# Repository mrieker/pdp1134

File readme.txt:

FPGA/ARM board that plugs into Unibus on PDP-11/34.

Provides functionality of the KY-11 console, 124KW memory,
RL-11 disks (RL01/RL02), DL-11 serial port, KW-11 line clock,
RH-11 disks (RP04/RP06), TM-11 tape drive, DELUA ethernet,
PC-11 paper tape reader/punch, DZ-11 serial line mux.

Also contains a PDP-11/34 processor simulator so can test
software without having real processor.

Has a GUI interface (ccode/z11gui) as well as a TCL command line
interface (ccode/z11ctrl) for scripting.

See howto.txt for more information.

Pics of board and gui screen are in boardpic.jpg and guittypic.png,
runningpic.jpg is pic of 10.5" screen mounted on front of PDP-11/34
with Zynq in place of console board.

It uses a ZTurn Zynq 7020 board for the FPGA/ARM processor,
memory, SDCARD, ethernet.  The ARM processor runs the
Raspberry PI OS, with a kernel specific to the Zynq.

The board might work on other PDP-11s, I haven't tested it
with anything else.  The only thing that makes it '34 specific
are the two halt signals.  Other than that, it is just another
Unibus compatible device, fitting in a quad-sized SPC slot.

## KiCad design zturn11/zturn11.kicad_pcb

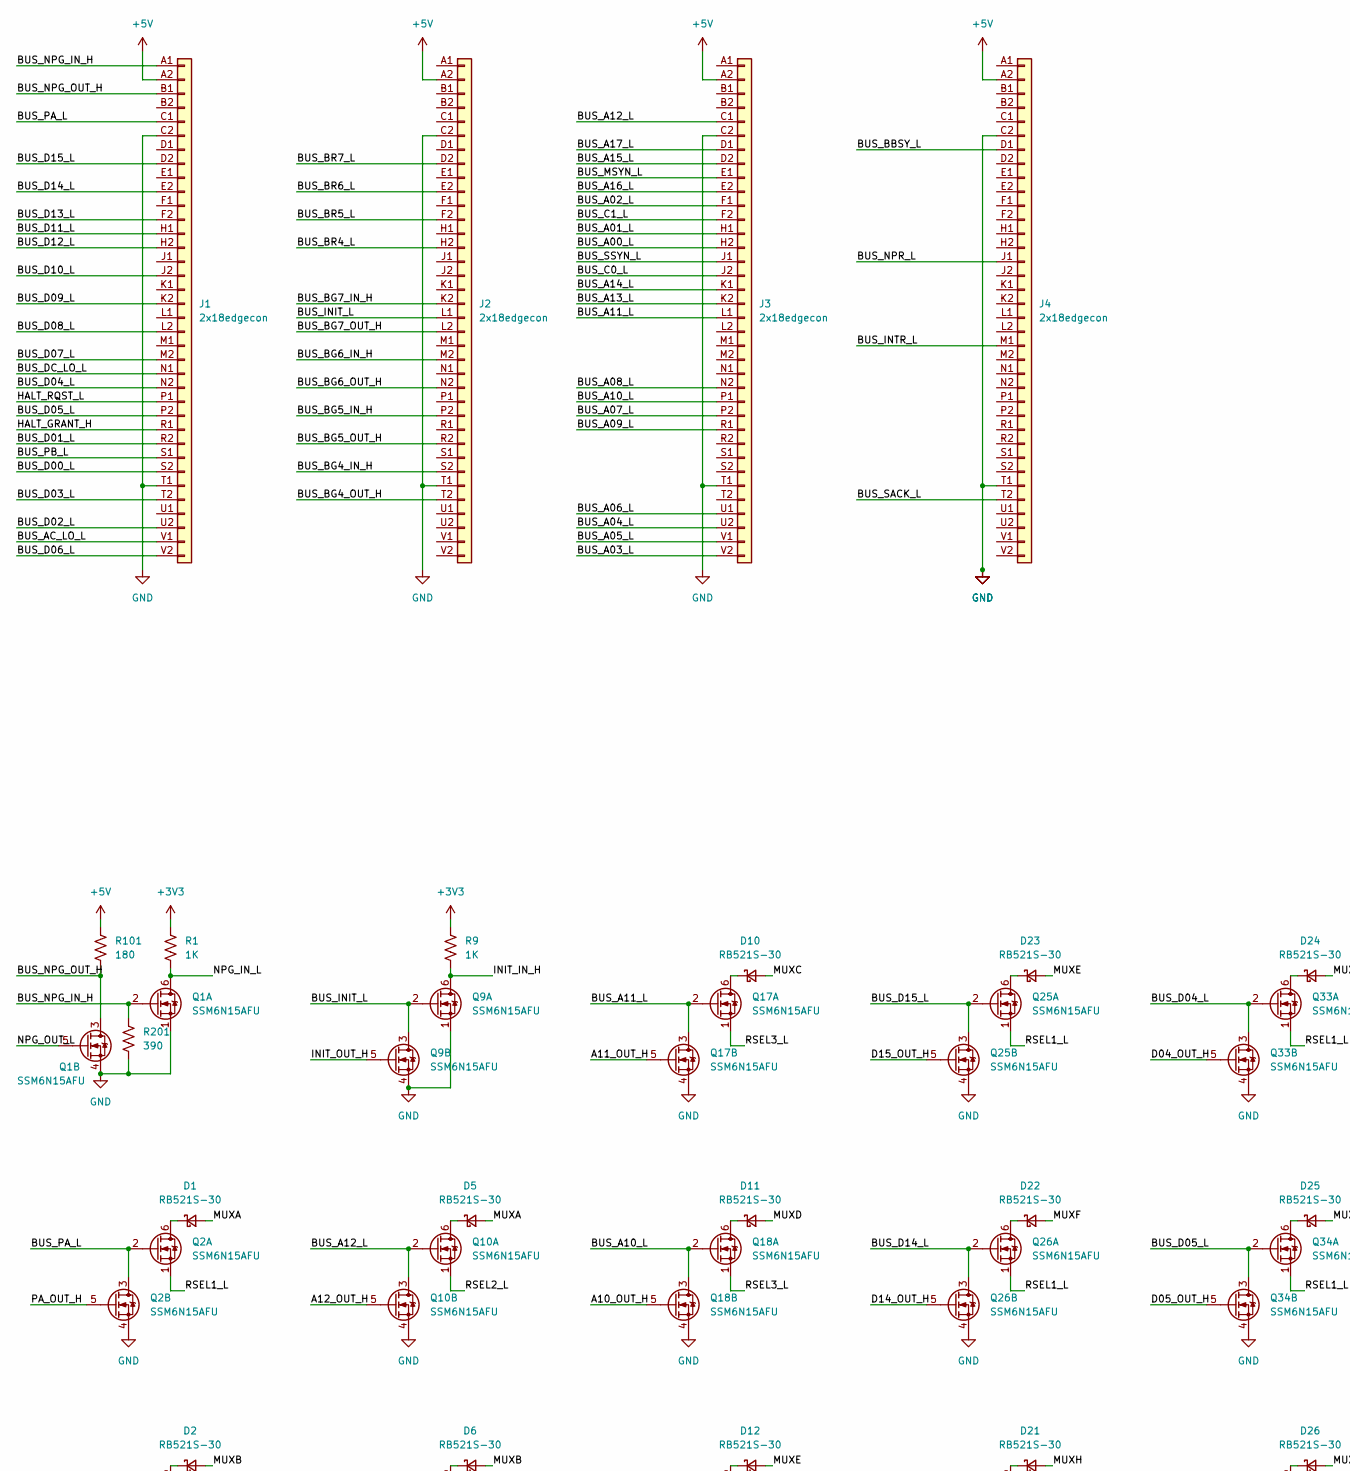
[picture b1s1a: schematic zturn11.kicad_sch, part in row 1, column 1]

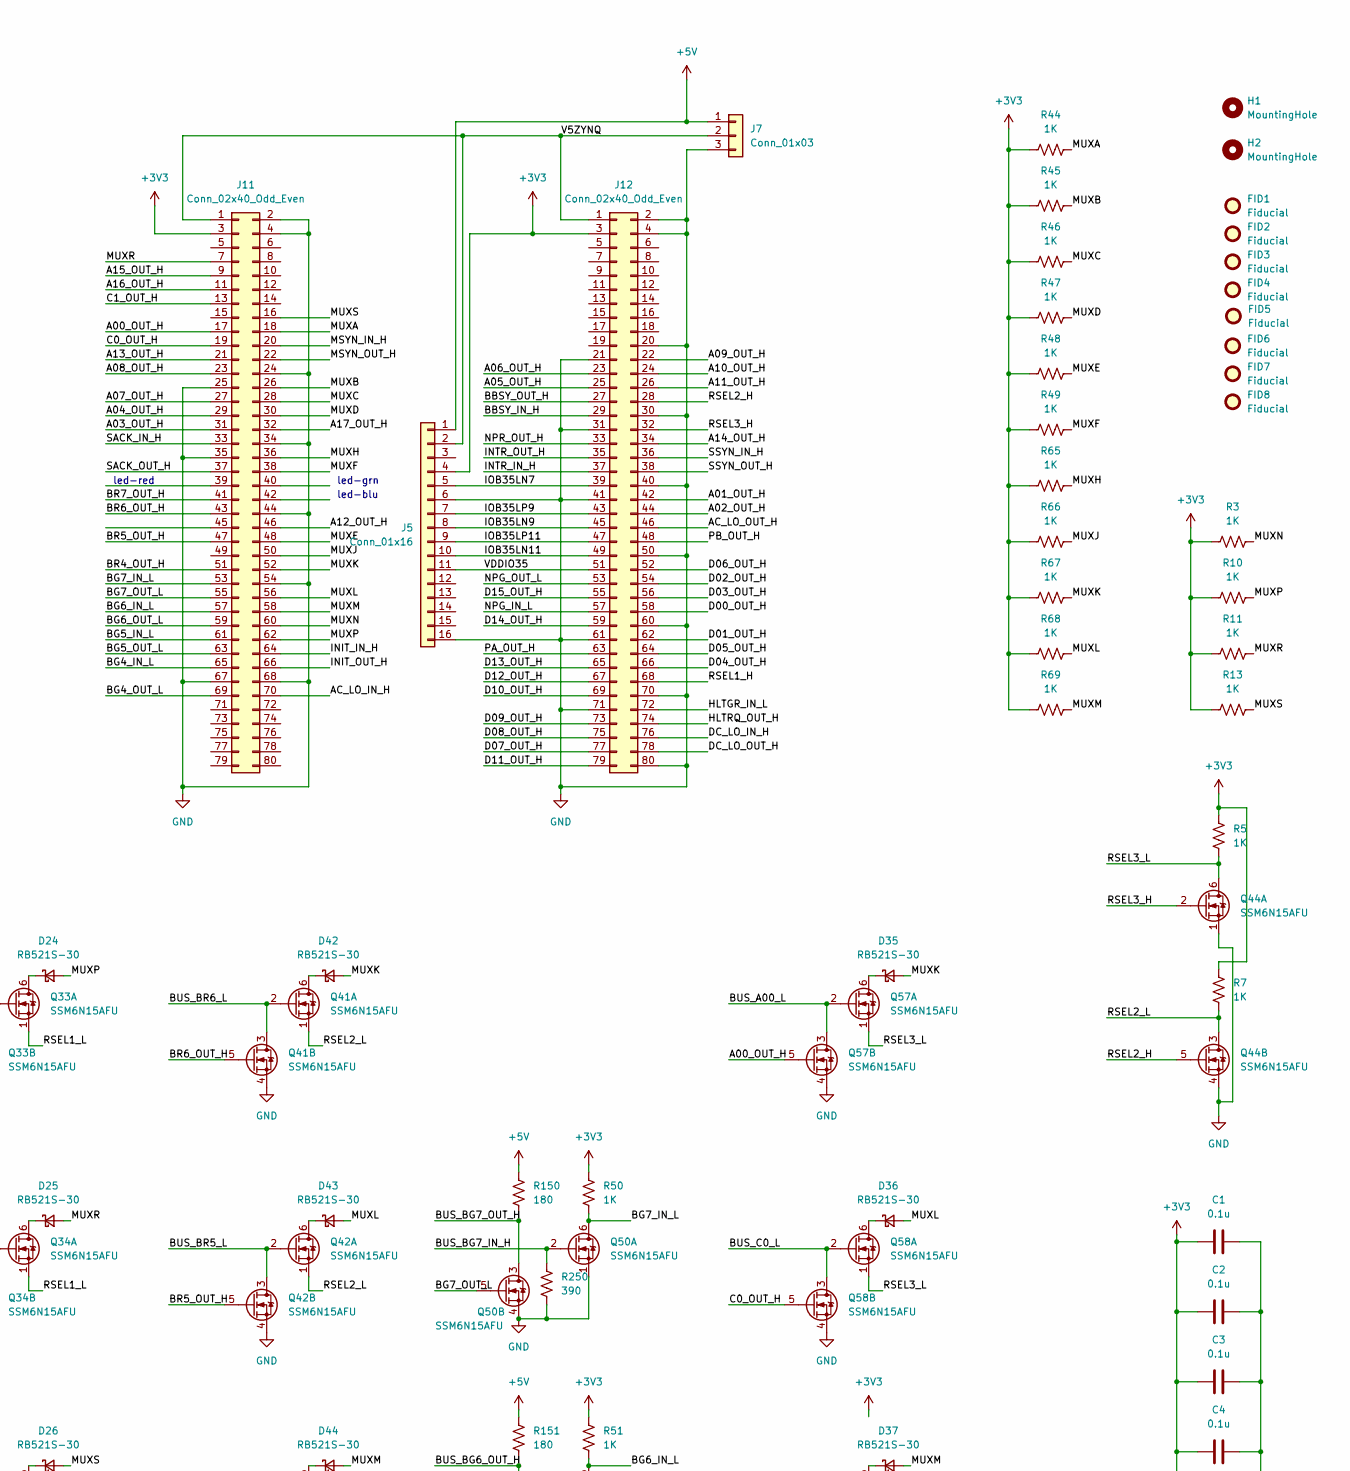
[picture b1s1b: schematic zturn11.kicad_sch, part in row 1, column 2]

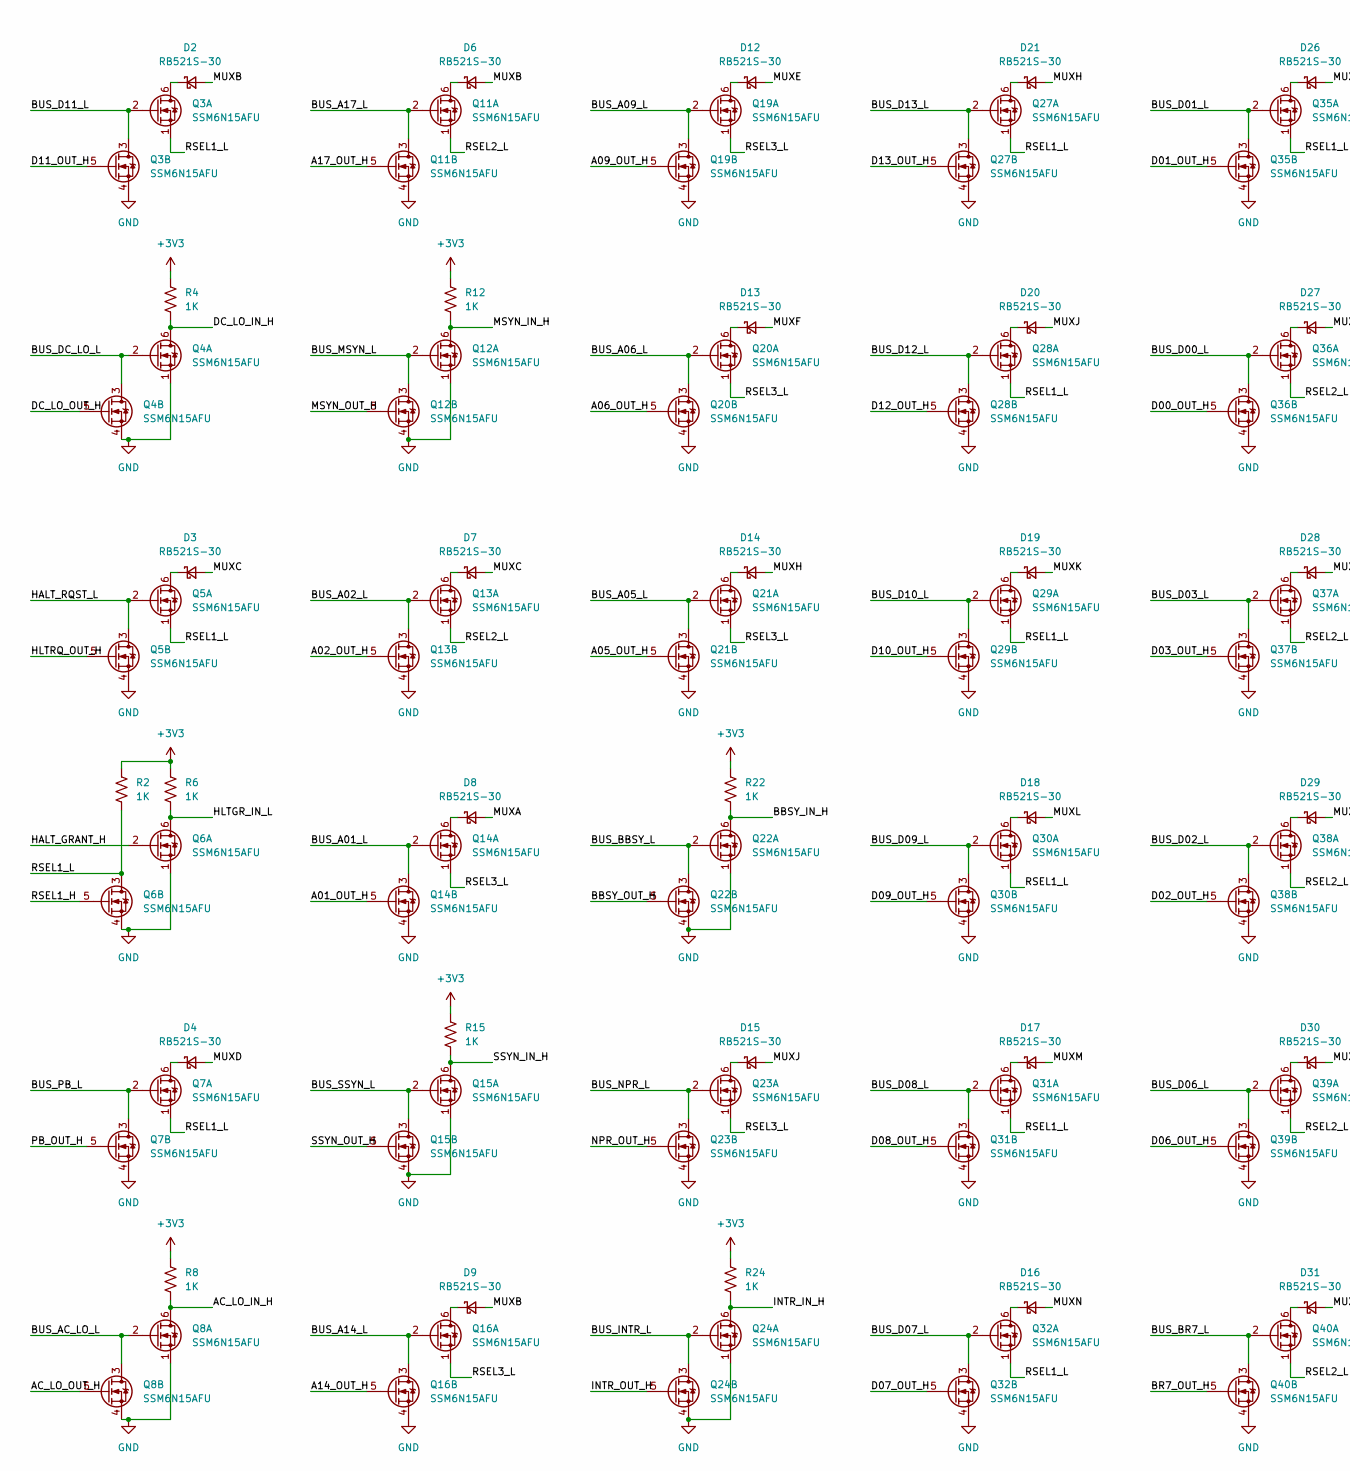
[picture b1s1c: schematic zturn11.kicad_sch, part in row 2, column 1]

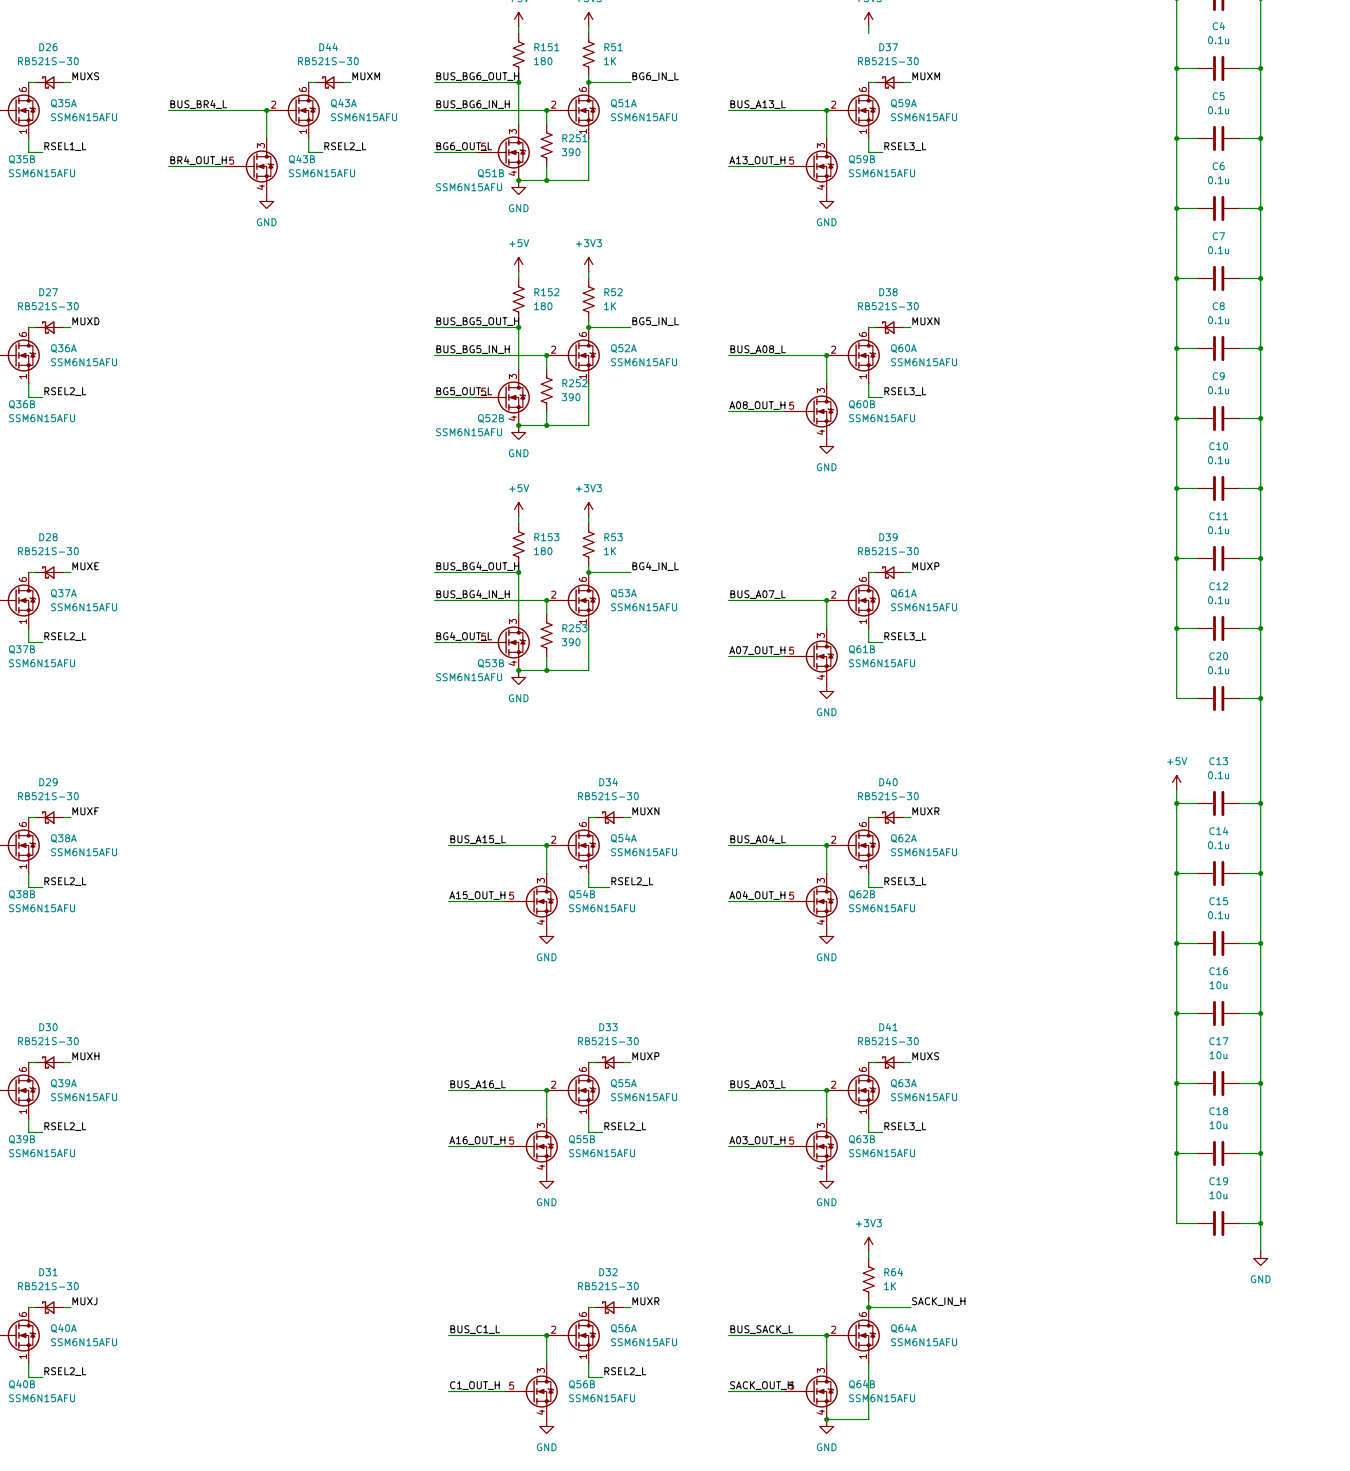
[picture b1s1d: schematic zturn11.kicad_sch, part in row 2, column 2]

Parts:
C1, C2, C3, C4, C5, C6, C7, C8, C9, C10, C11, C12, C13, C14, C15, C20: 0.1u; C_0402_1005Metric
C16, C17, C18, C19: 10u; C_1206_3216Metric
D1, D2, D3, D4, D5, D6, D7, D8, D9, D10, D11, D12, D13, D14, D15, D16, D17, D18, D19, D20, D21, D22, D23, D24, D25, D26, D27, D28, D29, D30, D31, D32, D33, D34, D35, D36, D37, D38, D39, D40, D41, D42, D43, D44: RB521S-30; D_SOD-523
FID1, FID2, FID3, FID4, FID5, FID6, FID7, FID8: Fiducial; Fiducial_1mm_Mask2mm
H1, H2: MountingHole; MountingHole_8.4mm_M8
J1, J2, J3, J4: 2x18edgecon; 2x18-edge
J5: Conn_01x16; PinHeader_1x16_P2.54mm_Horizontal
J7: Conn_01x03; PinHeader_1x03_P2.54mm_Horizontal
J11, J12: Conn_02x40_Odd_Even; PinHeader_2x40_P1.27mm_Vertical
Q1, Q2, Q3, Q4, Q5, Q6, Q7, Q8, Q9, Q10, Q11, Q12, Q13, Q14, Q15, Q16, Q17, Q18, Q19, Q20, Q21, Q22, Q23, Q24, Q25, Q26, Q27, Q28, Q29, Q30, Q31, Q32, Q33, Q34, Q35, Q36, Q37, Q38, Q39, Q40, Q41, Q42, Q43, Q44, Q50, Q51, Q52, Q53, Q54, Q55, Q56, Q57, Q58, Q59, Q60, Q61, Q62, Q63, Q64: SSM6N15AFU; SOT-363_SC-70-6
R1, R2, R3, R4, R5, R6, R7, R8, R9, R10, R11, R12, R13, R15, R22, R24, R44, R45, R46, R47, R48, R49, R50, R51, R52, R53, R64, R65, R66, R67, R68, R69: 1K; R_0402_1005Metric
R101, R150, R151, R152, R153: 180; R_0402_1005Metric
R201, R250, R251, R252, R253: 390; R_0402_1005Metric

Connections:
+3V3: C1.1, C2.1, C3.1, C4.1, C5.1, C6.1, C7.1, C8.1, C9.1, C10.1, C11.1, C12.1, C20.1, J5.4, J11.3, J12.3, R1.1, R2.1, R3.1, R4.1, R5.1, R6.1, R7.1, R8.1, R9.1, R10.1, R11.1, R12.1, R13.1, R15.1, R22.1, R24.1, R44.1, R45.1, R46.1, R47.1, R48.1, R49.1, R50.1, R51.1, R52.1, R53.1, R64.1, R65.1, R66.1, R67.1, R68.1, R69.1
+5V: C13.1, C14.1, C15.1, C16.1, C17.1, C18.1, C19.1, J1.A2, J2.A2, J3.A2, J4.A2, J5.1, J7.1, R101.1, R150.1, R151.1, R152.1, R153.1
/A00_OUT_H: J11.17, Q57.5 (G2)
/A01_OUT_H: J12.42, Q14.5 (G2)
/A02_OUT_H: J12.44, Q13.5 (G2)
/A03_OUT_H: J11.31, Q63.5 (G2)
/A04_OUT_H: J11.29, Q62.5 (G2)
/A05_OUT_H: J12.25, Q21.5 (G2)
/A06_OUT_H: J12.23, Q20.5 (G2)
/A07_OUT_H: J11.27, Q61.5 (G2)
/A08_OUT_H: J11.23, Q60.5 (G2)
/A09_OUT_H: J12.22, Q19.5 (G2)
/A10_OUT_H: J12.24, Q18.5 (G2)
/A11_OUT_H: J12.26, Q17.5 (G2)
/A12_OUT_H: J11.46, Q10.5 (G2)
/A13_OUT_H: J11.21, Q59.5 (G2)
/A14_OUT_H: J12.34, Q16.5 (G2)
/A15_OUT_H: J11.9, Q54.5 (G2)
/A16_OUT_H: J11.11, Q55.5 (G2)
/A17_OUT_H: J11.32, Q11.5 (G2)
/AC_LO_IN_H: J11.70, Q8.6 (D1), R8.2
/AC_LO_OUT_H: J12.46, Q8.5 (G2)
/BBSY_IN_H: J12.29, Q22.6 (D1), R22.2
/BBSY_OUT_H: J12.27, Q22.5 (G2)
/BG4_IN_L: J11.65, Q53.6 (D1), R53.2
/BG4_OUT_L: J11.69, Q53.5 (G2)
/BG5_IN_L: J11.61, Q52.6 (D1), R52.2
/BG5_OUT_L: J11.63, Q52.5 (G2)
/BG6_IN_L: J11.57, Q51.6 (D1), R51.2
/BG6_OUT_L: J11.59, Q51.5 (G2)
/BG7_IN_L: J11.53, Q50.6 (D1), R50.2
/BG7_OUT_L: J11.55, Q50.5 (G2)
/BR4_OUT_H: J11.51, Q43.5 (G2)
/BR5_OUT_H: J11.47, Q42.5 (G2)
/BR6_OUT_H: J11.43, Q41.5 (G2)
/BR7_OUT_H: J11.41, Q40.5 (G2)
/BUS_A00_L: J3.H2, Q57.2 (G1), Q57.3 (D2)
/BUS_A01_L: J3.H1, Q14.2 (G1), Q14.3 (D2)
/BUS_A02_L: J3.F1, Q13.2 (G1), Q13.3 (D2)
/BUS_A03_L: J3.V2, Q63.2 (G1), Q63.3 (D2)
/BUS_A04_L: J3.U2, Q62.2 (G1), Q62.3 (D2)
/BUS_A05_L: J3.V1, Q21.2 (G1), Q21.3 (D2)
/BUS_A06_L: J3.U1, Q20.2 (G1), Q20.3 (D2)
/BUS_A07_L: J3.P2, Q61.2 (G1), Q61.3 (D2)
/BUS_A08_L: J3.N2, Q60.2 (G1), Q60.3 (D2)
/BUS_A09_L: J3.R1, Q19.2 (G1), Q19.3 (D2)
/BUS_A10_L: J3.P1, Q18.2 (G1), Q18.3 (D2)
/BUS_A11_L: J3.L1, Q17.2 (G1), Q17.3 (D2)
/BUS_A12_L: J3.C1, Q10.2 (G1), Q10.3 (D2)
/BUS_A13_L: J3.K2, Q59.2 (G1), Q59.3 (D2)
/BUS_A14_L: J3.K1, Q16.2 (G1), Q16.3 (D2)
/BUS_A15_L: J3.D2, Q54.2 (G1), Q54.3 (D2)
/BUS_A16_L: J3.E2, Q55.2 (G1), Q55.3 (D2)
/BUS_A17_L: J3.D1, Q11.2 (G1), Q11.3 (D2)
/BUS_AC_LO_L: J1.V1, Q8.2 (G1), Q8.3 (D2)
/BUS_BBSY_L: J4.D1, Q22.2 (G1), Q22.3 (D2)
/BUS_BG4_IN_H: J2.S2, Q53.2 (G1), R253.1
/BUS_BG4_OUT_H: J2.T2, Q53.3 (D2), R153.2
/BUS_BG5_IN_H: J2.P2, Q52.2 (G1), R252.1
/BUS_BG5_OUT_H: J2.R2, Q52.3 (D2), R152.2
/BUS_BG6_IN_H: J2.M2, Q51.2 (G1), R251.1
/BUS_BG6_OUT_H: J2.N2, Q51.3 (D2), R151.2
/BUS_BG7_IN_H: J2.K2, Q50.2 (G1), R250.1
/BUS_BG7_OUT_H: J2.L2, Q50.3 (D2), R150.2
/BUS_BR4_L: J2.H2, Q43.2 (G1), Q43.3 (D2)
/BUS_BR5_L: J2.F2, Q42.2 (G1), Q42.3 (D2)
/BUS_BR6_L: J2.E2, Q41.2 (G1), Q41.3 (D2)
/BUS_BR7_L: J2.D2, Q40.2 (G1), Q40.3 (D2)
/BUS_C0_L: J3.J2, Q58.2 (G1), Q58.3 (D2)
/BUS_C1_L: J3.F2, Q56.2 (G1), Q56.3 (D2)
/BUS_D00_L: J1.S2, Q36.2 (G1), Q36.3 (D2)
/BUS_D01_L: J1.R2, Q35.2 (G1), Q35.3 (D2)
/BUS_D02_L: J1.U2, Q38.2 (G1), Q38.3 (D2)
/BUS_D03_L: J1.T2, Q37.2 (G1), Q37.3 (D2)
/BUS_D04_L: J1.N2, Q33.2 (G1), Q33.3 (D2)
/BUS_D05_L: J1.P2, Q34.2 (G1), Q34.3 (D2)
/BUS_D06_L: J1.V2, Q39.2 (G1), Q39.3 (D2)
/BUS_D07_L: J1.M2, Q32.2 (G1), Q32.3 (D2)
/BUS_D08_L: J1.L2, Q31.2 (G1), Q31.3 (D2)
/BUS_D09_L: J1.K2, Q30.2 (G1), Q30.3 (D2)
/BUS_D10_L: J1.J2, Q29.2 (G1), Q29.3 (D2)
/BUS_D11_L: J1.H1, Q3.2 (G1), Q3.3 (D2)
/BUS_D12_L: J1.H2, Q28.2 (G1), Q28.3 (D2)
/BUS_D13_L: J1.F2, Q27.2 (G1), Q27.3 (D2)
/BUS_D14_L: J1.E2, Q26.2 (G1), Q26.3 (D2)
/BUS_D15_L: J1.D2, Q25.2 (G1), Q25.3 (D2)
/BUS_DC_LO_L: J1.N1, Q4.2 (G1), Q4.3 (D2)
/BUS_INIT_L: J2.L1, Q9.2 (G1), Q9.3 (D2)
/BUS_INTR_L: J4.M1, Q24.2 (G1), Q24.3 (D2)
/BUS_MSYN_L: J3.E1, Q12.2 (G1), Q12.3 (D2)
/BUS_NPG_IN_H: J1.A1, Q1.2 (G1), R201.1
/BUS_NPG_OUT_H: J1.B1, Q1.3 (D2), R101.2
/BUS_NPR_L: J4.J1, Q23.2 (G1), Q23.3 (D2)
/BUS_PA_L: J1.C1, Q2.2 (G1), Q2.3 (D2)
/BUS_PB_L: J1.S1, Q7.2 (G1), Q7.3 (D2)
/BUS_SACK_L: J4.T2, Q64.2 (G1), Q64.3 (D2)
/BUS_SSYN_L: J3.J1, Q15.2 (G1), Q15.3 (D2)
/C0_OUT_H: J11.19, Q58.5 (G2)
/C1_OUT_H: J11.13, Q56.5 (G2)
/D00_OUT_H: J12.58, Q36.5 (G2)
/D01_OUT_H: J12.62, Q35.5 (G2)
/D02_OUT_H: J12.54, Q38.5 (G2)
/D03_OUT_H: J12.56, Q37.5 (G2)
/D04_OUT_H: J12.66, Q33.5 (G2)
/D05_OUT_H: J12.64, Q34.5 (G2)
/D06_OUT_H: J12.52, Q39.5 (G2)
/D07_OUT_H: J12.77, Q32.5 (G2)
/D08_OUT_H: J12.75, Q31.5 (G2)
/D09_OUT_H: J12.73, Q30.5 (G2)
/D10_OUT_H: J12.69, Q29.5 (G2)
/D11_OUT_H: J12.79, Q3.5 (G2)
/D12_OUT_H: J12.67, Q28.5 (G2)
/D13_OUT_H: J12.65, Q27.5 (G2)
/D14_OUT_H: J12.59, Q26.5 (G2)
/D15_OUT_H: J12.55, Q25.5 (G2)
/DC_LO_IN_H: J12.76, Q4.6 (D1), R4.2
/DC_LO_OUT_H: J12.78, Q4.5 (G2)
/HALT_GRANT_H: J1.R1, Q6.2 (G1)
/HALT_RQST_L: J1.P1, Q5.2 (G1), Q5.3 (D2)
/HLTGR_IN_L: J12.72, Q6.6 (D1), R6.2
/HLTRQ_OUT_H: J12.74, Q5.5 (G2)
/INIT_IN_H: J11.64, Q9.6 (D1), R9.2
/INIT_OUT_H: J11.66, Q9.5 (G2)
/INTR_IN_H: J12.37, Q24.6 (D1), R24.2
/INTR_OUT_H: J12.35, Q24.5 (G2)
/IOB35LN7: J5.5, J12.39
/IOB35LN9: J5.8, J12.45
/IOB35LN11: J5.10, J12.49
/IOB35LP9: J5.7, J12.43
/IOB35LP11: J5.9, J12.47
/MSYN_IN_H: J11.20, Q12.6 (D1), R12.2
/MSYN_OUT_H: J11.22, Q12.5 (G2)
/MUXA: D1.2 (A), D5.2 (A), D8.2 (A), J11.18, R44.2
/MUXB: D2.2 (A), D6.2 (A), D9.2 (A), J11.26, R45.2
/MUXC: D3.2 (A), D7.2 (A), D10.2 (A), J11.28, R46.2
/MUXD: D4.2 (A), D11.2 (A), D27.2 (A), J11.30, R47.2
/MUXE: D12.2 (A), D23.2 (A), D28.2 (A), J11.48, R48.2
/MUXF: D13.2 (A), D22.2 (A), D29.2 (A), J11.38, R49.2
/MUXH: D14.2 (A), D21.2 (A), D30.2 (A), J11.36, R65.2
/MUXJ: D15.2 (A), D20.2 (A), D31.2 (A), J11.50, R66.2
/MUXK: D19.2 (A), D35.2 (A), D42.2 (A), J11.52, R67.2
/MUXL: D18.2 (A), D36.2 (A), D43.2 (A), J11.56, R68.2
/MUXM: D17.2 (A), D37.2 (A), D44.2 (A), J11.58, R69.2
/MUXN: D16.2 (A), D34.2 (A), D38.2 (A), J11.60, R3.2
/MUXP: D24.2 (A), D33.2 (A), D39.2 (A), J11.62, R10.2
/MUXR: D25.2 (A), D32.2 (A), D40.2 (A), J11.7, R11.2
/MUXS: D26.2 (A), D41.2 (A), J11.16, R13.2
/NPG_IN_L: J12.57, Q1.6 (D1), R1.2
/NPG_OUT_L: J12.53, Q1.5 (G2)
/NPR_OUT_H: J12.33, Q23.5 (G2)
/PA_OUT_H: J12.63, Q2.5 (G2)
/PB_OUT_H: J12.48, Q7.5 (G2)
/RSEL1_H: J12.68, Q6.5 (G2)
/RSEL1_L: Q2.1 (S1), Q3.1 (S1), Q5.1 (S1), Q6.3 (D2), Q7.1 (S1), Q25.1 (S1), Q26.1 (S1), Q27.1 (S1), Q28.1 (S1), Q29.1 (S1), Q30.1 (S1), Q31.1 (S1), Q32.1 (S1), Q33.1 (S1), Q34.1 (S1), Q35.1 (S1), R2.2
/RSEL2_H: J12.28, Q44.5 (G2)
/RSEL2_L: Q10.1 (S1), Q11.1 (S1), Q13.1 (S1), Q36.1 (S1), Q37.1 (S1), Q38.1 (S1), Q39.1 (S1), Q40.1 (S1), Q41.1 (S1), Q42.1 (S1), Q43.1 (S1), Q44.3 (D2), Q54.1 (S1), Q55.1 (S1), Q56.1 (S1), R7.2
/RSEL3_H: J12.32, Q44.2 (G1)
/RSEL3_L: Q14.1 (S1), Q16.1 (S1), Q17.1 (S1), Q18.1 (S1), Q19.1 (S1), Q20.1 (S1), Q21.1 (S1), Q23.1 (S1), Q44.6 (D1), Q57.1 (S1), Q58.1 (S1), Q59.1 (S1), Q60.1 (S1), Q61.1 (S1), Q62.1 (S1), Q63.1 (S1), R5.2
/SACK_IN_H: J11.33, Q64.6 (D1), R64.2
/SACK_OUT_H: J11.37, Q64.5 (G2)
/SSYN_IN_H: J12.36, Q15.6 (D1), R15.2
/SSYN_OUT_H: J12.38, Q15.5 (G2)
/V5ZYNQ: J5.2, J7.2, J11.1, J12.1
/VDDIO35: J5.11, J12.51
GND: C1.2, C2.2, C3.2, C4.2, C5.2, C6.2, C7.2, C8.2, C9.2, C10.2, C11.2, C12.2, C13.2, C14.2, C15.2, C16.2, C17.2, C18.2, C19.2, C20.2, J1.C2, J1.T1, J2.C2, J2.T1, J3.C2, J3.T1, J4.C2, J4.T1, J5.6, J5.16, J7.3, J11.2, J11.4, J11.24, J11.25, J11.34, J11.35, J11.44, J11.54, J11.67, J11.68, J12.2, J12.4, J12.20, J12.21, J12.30, J12.31, J12.40, J12.41, J12.50, J12.60, J12.61, J12.70, J12.71, J12.80, Q1.1 (S1), Q1.4 (S2), Q2.4 (S2), Q3.4 (S2), Q4.1 (S1), Q4.4 (S2), Q5.4 (S2), Q6.1 (S1), Q6.4 (S2), Q7.4 (S2), Q8.1 (S1), Q8.4 (S2), Q9.1 (S1), Q9.4 (S2), Q10.4 (S2), Q11.4 (S2), Q12.1 (S1), Q12.4 (S2), Q13.4 (S2), Q14.4 (S2), Q15.1 (S1), Q15.4 (S2), Q16.4 (S2), Q17.4 (S2), Q18.4 (S2), Q19.4 (S2), Q20.4 (S2), Q21.4 (S2), Q22.1 (S1), Q22.4 (S2), Q23.4 (S2), Q24.1 (S1), Q24.4 (S2), Q25.4 (S2), Q26.4 (S2), Q27.4 (S2), Q28.4 (S2), Q29.4 (S2), Q30.4 (S2), Q31.4 (S2), Q32.4 (S2), Q33.4 (S2), Q34.4 (S2), Q35.4 (S2), Q36.4 (S2), Q37.4 (S2), Q38.4 (S2), Q39.4 (S2), Q40.4 (S2), Q41.4 (S2), Q42.4 (S2), Q43.4 (S2), Q44.1 (S1), Q44.4 (S2), Q50.1 (S1), Q50.4 (S2), Q51.1 (S1), Q51.4 (S2), Q52.1 (S1), Q52.4 (S2), Q53.1 (S1), Q53.4 (S2), Q54.4 (S2), Q55.4 (S2), Q56.4 (S2), Q57.4 (S2), Q58.4 (S2), Q59.4 (S2), Q60.4 (S2), Q61.4 (S2), Q62.4 (S2), Q63.4 (S2), Q64.1 (S1), Q64.4 (S2), R201.2, R250.2, R251.2, R252.2, R253.2
unnamed: D1.1 (K), Q2.6 (D1)
unnamed: D2.1 (K), Q3.6 (D1)
unnamed: D3.1 (K), Q5.6 (D1)
unnamed: D4.1 (K), Q7.6 (D1)
unnamed: D5.1 (K), Q10.6 (D1)
unnamed: D6.1 (K), Q11.6 (D1)
unnamed: D7.1 (K), Q13.6 (D1)
unnamed: D8.1 (K), Q14.6 (D1)
unnamed: D9.1 (K), Q16.6 (D1)
unnamed: D10.1 (K), Q17.6 (D1)
unnamed: D11.1 (K), Q18.6 (D1)
unnamed: D12.1 (K), Q19.6 (D1)
unnamed: D13.1 (K), Q20.6 (D1)
unnamed: D14.1 (K), Q21.6 (D1)
unnamed: D15.1 (K), Q23.6 (D1)
unnamed: D16.1 (K), Q32.6 (D1)
unnamed: D17.1 (K), Q31.6 (D1)
unnamed: D18.1 (K), Q30.6 (D1)
unnamed: D19.1 (K), Q29.6 (D1)
unnamed: D20.1 (K), Q28.6 (D1)
unnamed: D21.1 (K), Q27.6 (D1)
unnamed: D22.1 (K), Q26.6 (D1)
unnamed: D23.1 (K), Q25.6 (D1)
unnamed: D24.1 (K), Q33.6 (D1)
unnamed: D25.1 (K), Q34.6 (D1)
unnamed: D26.1 (K), Q35.6 (D1)
unnamed: D27.1 (K), Q36.6 (D1)
unnamed: D28.1 (K), Q37.6 (D1)
unnamed: D29.1 (K), Q38.6 (D1)
unnamed: D30.1 (K), Q39.6 (D1)
unnamed: D31.1 (K), Q40.6 (D1)
unnamed: D32.1 (K), Q56.6 (D1)
unnamed: D33.1 (K), Q55.6 (D1)
unnamed: D34.1 (K), Q54.6 (D1)
unnamed: D35.1 (K), Q57.6 (D1)
unnamed: D36.1 (K), Q58.6 (D1)
unnamed: D37.1 (K), Q59.6 (D1)
unnamed: D38.1 (K), Q60.6 (D1)
unnamed: D39.1 (K), Q61.6 (D1)
unnamed: D40.1 (K), Q62.6 (D1)
unnamed: D41.1 (K), Q63.6 (D1)
unnamed: D42.1 (K), Q41.6 (D1)
unnamed: D43.1 (K), Q42.6 (D1)
unnamed: D44.1 (K), Q43.6 (D1)

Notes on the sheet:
led-red
led-grn
led-blu

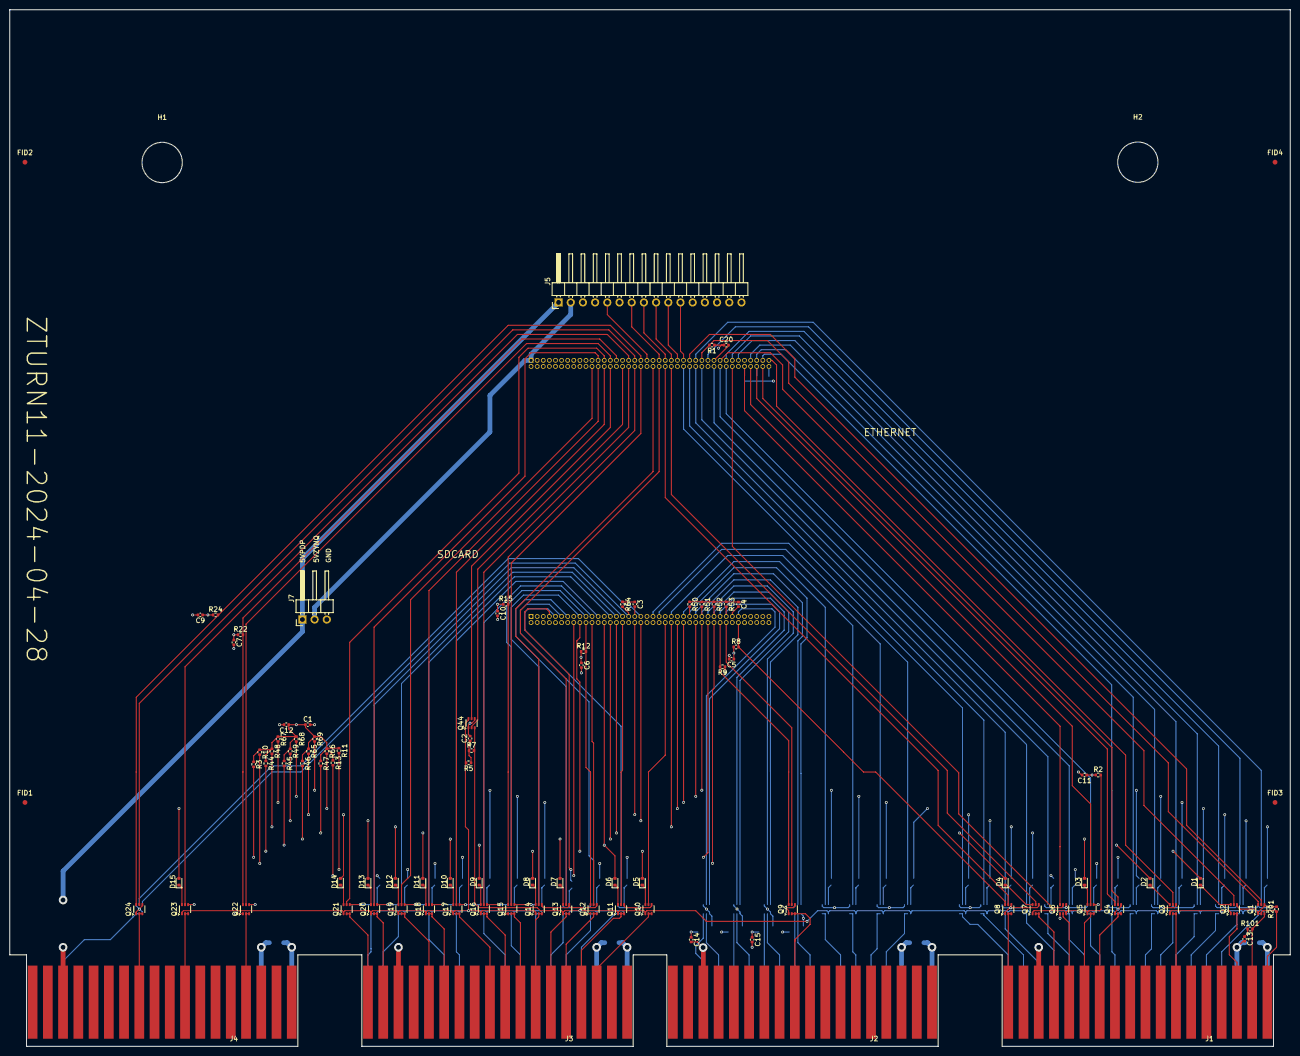
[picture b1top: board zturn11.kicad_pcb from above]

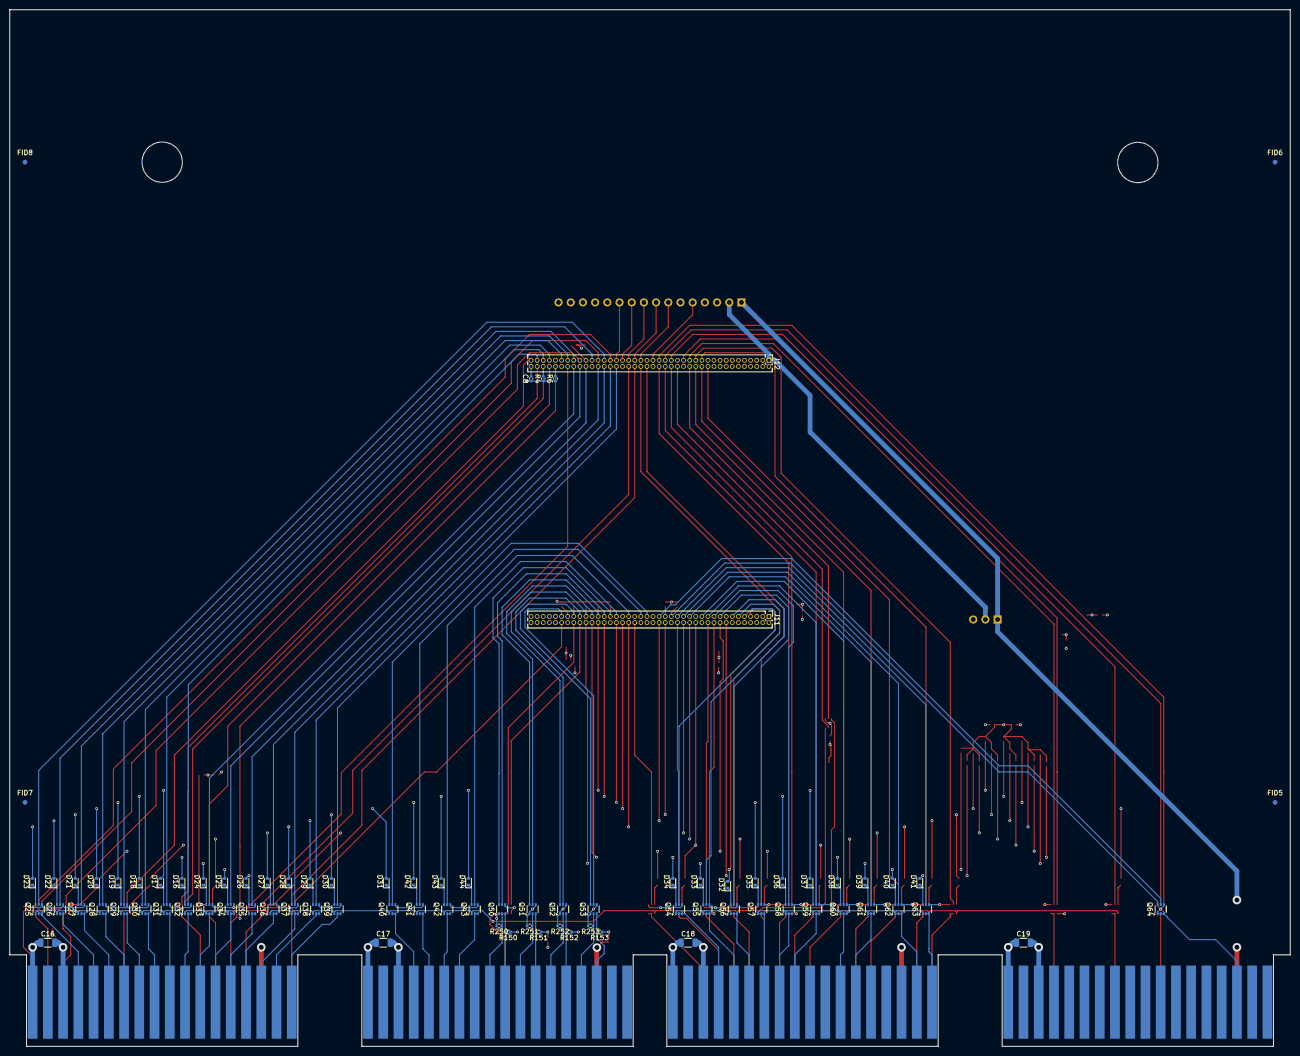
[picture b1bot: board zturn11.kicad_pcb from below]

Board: 4 copper layers, 266.7 x 215.9 mm, 183 parts (84 on the bottom side), 209 nets.

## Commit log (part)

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2025-04-25 initial commit
    - board works
    have to patch line BR6_OUT_H from J11-45 to J12-47/J5-14
    (J11-45 is connected to a 12MHz oscillator on ZTurn board)
2025-04-25 add bunch of stuff
    add z11dump program, update pin list for pin command
    fpga: interrupt controller, little memory, serial line controller
2025-04-28 add diodes to the zturn11 board so the muxes work
    also add AC_LO_OUT_H and DC_LO_OUT_H drivers
2025-04-29 add AC_LO_OUT_H and DC_LO_OUT_H signals for new circuit board
2025-04-30 get simulator DIV, ASH, ASHC working
2025-05-01 add odd address/bus timeout handling to simulator
2025-05-03 re-arrange simulator code
    have memory access state machine automatically block
    operand address state machine and main cpu state machine
    have operand address state machine block main cpu state machine
    main cpu state machine steps only when the other two are idle
2025-05-03 rename simulator signals to include _in_ and _out_ where needed
    only change was to add bus_bbsy_out_l to sim
2025-05-04 have fpgamode off reset all fpga circuitry
2025-05-05 add simple cpu test
    ./z11ctrl
    > source test.tcl
    > test1
    increments R0 and prints every 100mS
2025-05-06 add z11dl program for accessing DL-11 tty
    also add some bits to swlight.v
    - read state of aclo,dclo,init signals
2025-05-07 move utility functions from test.tcl to z11ctrlini.tcl
2025-05-10 get swlight halted detection to work
2025-05-10 make csv files of bus signals within zynq.v
2025-05-11 add ilactl fields to dump output
2025-05-16 add parity to bigmem
    but it doesn't report errors to pdp yet
2025-05-17 add sl_haltins flag to indicate processor halted on its own
    detected by seeing unibus hltrq asserted when not being requested by sl_hltrq
2025-05-19 get swlight.v dma working
    test script:
    source inclooptest.tcl
    start ;# gets is running
    loop ;# does a dma transfer every 200mS
2025-05-21 update verilator with whole board and multiple processes
2025-05-23 get interrupts working
    test:
    $ ./z11ctrl
    > source inttest.tcl
    > loadtest
    > runtest
2025-05-24 get rltest.mac to test 3 drives at once
    pounds the living daylights out of it
2025-05-25 get simulator working with rltest.mac
    see top of rltest.mac for test
    use 'pin set fpgamode 1' instead of ... 2
2025-05-26 second pass at GUI
    get some little stuff working
    * recover from timed-out memory access
    * fix reset function
    display messages at bottom saying what happened
2025-05-26 update verisim
    also keep DL11 from babbling when INIT is asserted
2025-05-28 start of simmer software simulator
    compile on x86 and ccode directory on x86
    run ./simmer.x86_64 in one screen
    then run z11xx programs on same x86 in another screen
2025-05-29 change simmer to use shared memory page instead of tcp
    much faster
2025-05-29 get rltest running on simmer
2025-05-30 fixes for sim1134.v working with maindec dfkaa
    > pin set fpgamode 1 bm_enablo 0xFFFFFFFF
    > hardreset
    > loadbin dfkaa.bin
    > wrword 0777707 0200
    > steptraceloop
2025-06-01 updates for disassembler, rl-11 and simmer cpu
2025-06-01 have rl11.v clear error bits immediately upon PDP writing RLCS
    RT-11 checks mask 100200 to test for ready, not just RLCS<07>
2025-06-01 fix KL-11 interrupt request so RT-11 boots
    $ ./z11ctrl
    > source testrt11.tcl
    > rt11initsim .. to use simmer or sim1134 simulator
    > rt11boot
    > rt11initreal .. to use real PDP with memory
    > rt11boot
2025-06-03 add scripts to run maindecs dfkaa,b,c
2025-06-04 add WAIT instruction support to simmer/cpu1134.cc
2025-06-06 get java GUI lights working over network
    on zturn: ./GUI -listen 54321
    on X-window: ./GUI -connect zturn:54321
    can do intermediate node forwarding:
    ./GUI -listen 54321 -connect zturn:54321
    also, wrap dmalock/unlock around whole sector so it
    doesn't lock/unlock for each word transferred, and
2025-06-06 set up a 50Hz mode bit for the line clock
2025-06-07 add virt/phys addresses to GUI
2025-06-07 add neon-style buttons to GUI
2025-06-08 remove client/server from GUI.java
2025-06-08 add fpga bigmem.v enable checkbox to GUI screen
    for SIM mode, enables all 124KW
    for REAL mode,
    - turns off all bigmem.v memory
    - scans real memory to see what's there
    - fills in missing pages with bigmem.v
2025-06-09 add RL-11 enable checkbox to GUI screen
2025-06-09 get GUI things to fit better
    removed border from leds
    buttons are exactly 2 x led size
2025-06-09 add textured panels to GUI screen
    ...and don't unload drives when disabling RL-11
2025-06-09 have GUI check for FPGA mode OFF before reading/writing memory
    ...so it doesn't hang or crash
2025-06-10 make z11ctrl rlload,rlstat,rlunload commands
    and make z11rl just a daemon process
2025-06-10 add rl02 file chooser to GUI RL02 LOAD button
    and prefix filenames with current directory
    and compress out /../ and /./
2025-06-12 have bigmem boot mem jamming accept PC,PS reading in either order
2025-06-12 fix file locking in z11rl
    use F_OFD_SETLK
    also fix starting up z11rl process so it doesn't zombie
2025-06-12 turn 777570 lights & switches rows on/off depending on KY-11 enable
2025-06-12 double click GUI RESET button instead of are you sure box
    also blank out PHYS/VIRT of address label when KY-11 disabled
2025-06-13 simplify GUI button enables
    simplify line clock enable
    reduce fpga mode select to single checkbox
2025-06-14 fix out-e-11 (aka rt-11) boot
    need to reset rwstate when it throws an mm exception
2025-06-14 fix gui rl file chooser to do single-click on directory for touchscreen
    also make sure boot menu has flushed last char to tty before booting
2025-06-15 get high-speed paper tape reader/punch working
2025-06-17 add support for RL01 drives
    files loaded must end with either .rl01 or .rl02
2025-06-19 remove cpu error register from 11/34 sim
2025-06-20 add tooltip text for gui buttons
    and long-press on RESET avoids confirmation prompt
2025-06-21 fix up some traps in sim1134.v
    JMP/JSR register - trap 004 instead of 010
    yellow stack check inhibited for just yellow stack traps, not all 004 traps
2025-06-22 shorten KY-11 DMA end cycle delays from 150nS to 80nS
    the 150nS delay only applies to MSYN at beginning of cycle
2025-06-22 add testsysgen.tcl test script to generate rsx system
    pounds disk, memory, processor
    runs on simulator or real processor
2025-06-25 add TM-11 drive support
2025-06-26 add TM-11 interrupt when rewind completes
    gui shows TM-11 interrupt count in R0 on wait or halt
    wait R0 displays only when in SIM mode
2025-06-29 fix ky-11 step function with cache board
    also fix a bunch of lint things found with verisim
2025-07-01 consolidate common RL,TM handling code
    also get daemonizing z11rl,z11tm to work
2025-07-02 have snapregs work when processor already halted
    snapregs always sets haltreq when it starts to halt processor while it reads registers
    it used to always clear haltreq when it finished to let the processor continue
    now it can either leave haltreq set or clear haltreq when it finishes
2025-07-03 swallow daemon() exited process so it doesn't zombie
2025-07-03 consolidate z11ctrl's rl & tm code
2025-07-04 let gui create empty disk and tape files
    type name in file name box then click Open button
2025-07-06 wrap z11xe dma operations with dmalock()/dmaunlk() for efficiency
    also define symbols for status bits
2025-07-08 fix tm11 rewind/unload status not resetting
    also update current tape position continuously while rewinding for gui
    and add -create option to tmload to create an empty tape file
2025-07-10 split tape functionality from z11tm.cc into tapelib.cc
    to make it easier to support other tape drives
2025-07-12 for TM-11, set end-of-tape only when writing
    ...otherwise BRU gets upset reading past where EOT marker would be
    also set DEUNA to use IRQ 5
    also discard nulls and redundant CRs when reading tty from tcl scripts
2025-07-14 add paper tape boot option to gui boot button menu
2025-07-16 get rsx4.5 decnet working with delua
    - change z11xe from deuna to delua
    decnet uploads mystery microcode to deuna but leaves delua as is
    - reset should set DNI when complete
    - fill in source address when transmitting packet
    - do level-triggered interrupts instead of edge-triggered
    - support loopback mode
2025-07-16 add dllock, dlunlock commands to z11ctrl
    use in scripts to make sure z11dl isn't running
    so replytoprompt, waitforstring, etc will work
    also default DZ-11 line speed to 960 cps just like DL-11
2025-07-17 show R0 in gui data display even when using real PDP
    ...so lights roll for RSX when idle
2025-07-18 redo dmalock/dmaunlk with a shared memory futex
    ky_dmalock didn't work
    boot rsx45/dlsym.rl02 disk
    test with 'dnping pdp11' loop on pdpi
    do 'pip [*,*]/li' on the pdp11
    - ran it for 45 mins
    used to fail in just a couple mins
2025-07-18 remove dmachecklocked() debugging calls & dmalock shared memory
2025-07-18 add pthread mutex back into dmalock()/dmaunlk()
2025-07-20 get basic RH-11 RP04/06 functions working
2025-07-21 have rh11 controller ready bit be just for data transfer commands
2025-07-24 add RH-11 checkbox to GUI screen
2025-07-25 don't reset RH-11 MOL,WRL,DT bits on bus init
    also fix disk name in rsx45sysgen-rp04.tcl script
2025-07-27 add tmboot.mac to repo
2025-07-30 update gui boot menu tty message
2025-07-31 add tmboot option to gui boot menu
2025-08-01 don't clear rh11 vol valid on controller clear function
    ...only clear on fpga power-up/reset or file load
2025-08-03 guiboot: don't probe devs and mem som user can select
    also start z11xe if delua enabled
2025-08-06 implement all wacky RH-11 interrupt conditions
    ...so rsts/e 10.1 will work
2025-08-07 add stuff needed to build FPGA code
    copied from pdp8l repo
    also include BOOT.BIN.gz and image.ub (compiled zynq boot files)
2025-08-09 add tpctotap utility to convert tpc tape files to tap tape files
    the tu10 tape drive only takes tap files
2025-08-09 have z11dl send out rsts/e date/time prompt reply strings
2025-08-14 add scripts for booting rsx
2025-08-14 fix z11xe to default ethernet to first 'e' network device
2025-08-16 get rid of useless simmer
2025-08-17 move boot menu to need ? to display menu
2025-08-21 have pidp data switch push run gui boot script
2025-08-23 fix up halt instruction in presence of z11pidp server running
2025-08-28 get more xxdp diags to run on sim
    113 FKAAC0.BIC 3-MAR-83 24 004411
    114 FKABD1.BIC 27-OCT-83 15 004441
    115 FKACA0.BIC 3-MAR-83 16 004460
    117 FKTGC0.BIC 3-MAR-83 17 004545
    118 FKTHB0.BIC 3-MAR-83 44 004566
    765 FKTAA0.BIC 11-AUG-76 17 036234
2025-08-30 get ZRLHB0 maindec working
    .R ZRLH??
    ZRLHB0.BIC
    DRSD0
    CZRLH-B-0
    CZRLH TESTS WRITE DATA, READ DATA, AND WRITE CHECK OPERATIONS
    UNIT IS RL01,RL02
2025-09-07 add ishalted command to z11ctrlini.tcl
    blocks snapregs while reading ky_halted flag
2025-09-12 uniform floatingpoint overflow/underflow processing
2025-09-12 get a little more of FFPBA0 working
2025-09-12 get LDCyx and STCxy working on sim fpu
2025-09-12 get FFPAA1 maindec working on sim
    just update top 32 bits of FAC when doing single-precision mode
    leave the bottom 32 bits intact
    means have to do rounding before storing value in FAC
2025-09-12 update fpaa.tcl fpab.tcl scripts to use ishalted
    so they don't quit with gui or pidp11 panel running
2025-09-14 add rundiags.tcl script to run the processor maindecs
2025-09-15 chip away at getting FFPCB0 working on sim FPU
    FFPAA1 and FFPBA0 run without error
2025-09-16 move block memory from block diagram to internal to bigmem.v
2025-09-24 fix simulator power-up vector reading initial PSW
